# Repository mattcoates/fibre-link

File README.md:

# Optical Fibre Link Project

This repository contains the results and scripts used for the testing of our optical fibre link.

## Clock Recovery
Scripts and results of the tests carried out on the FPGA that was performing clock recovery.

## Error Rate
Testing of the BER of the complete link.

## Header Detection
Scripts and results of the tests on the header detector.

## Image Testing
Results of using the link to transmit an image at different frequencies. 

## PRBS
Characterisation of a pseudo-random number generator used to generate dummy data to test the link.

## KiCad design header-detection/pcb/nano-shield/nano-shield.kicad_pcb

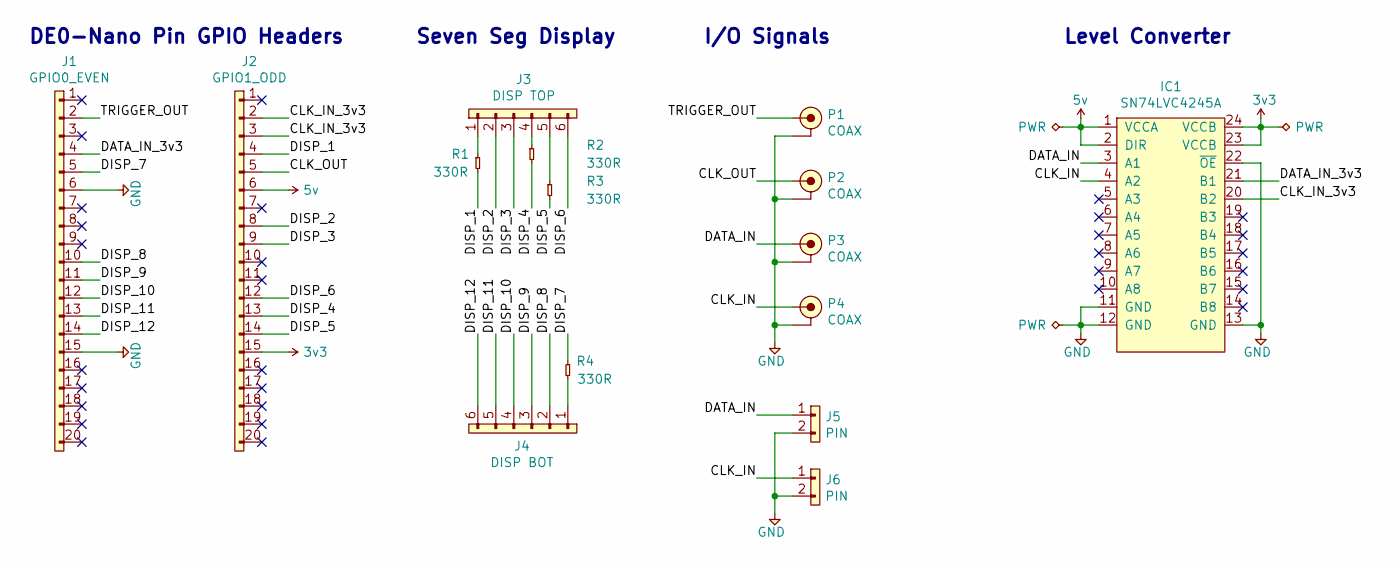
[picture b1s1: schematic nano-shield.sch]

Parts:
IC1: SN74LVC4245A; TSSOP-24; Farnell 1236393
J1: GPIO0_EVEN; SIL-254P-20
J2: GPIO1_ODD; SIL-254P-20
J3: DISP TOP; SIL-254P-06
J4: DISP BOT; SIL-254P-06
J5, J6: PIN; SIL-254P-02
P1, P2, P3, P4: COAX; SMA-EDGE; Farnell 1608592
R1, R2, R3, R4: 330R; 0805

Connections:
3v3: IC1.23 (VCCB), IC1.24 (VCCB), J2.15
5v: IC1.1 (VCCA), IC1.2 (DIR), J2.6
/CLK_IN: IC1.4 (A2), J6.1, P4.1 (RF)
/CLK_IN_3v3: IC1.20 (B2), J2.2, J2.3
/CLK_OUT: J2.5, P2.1 (RF)
/DATA_IN: IC1.3 (A1), J5.1, P3.1 (RF)
/DATA_IN_3v3: IC1.21 (B1), J1.4
/DISP_1: J2.4, R1.2
/DISP_2: J2.8, J3.2
/DISP_3: J2.9, J3.3
/DISP_4: J2.13, R2.2
/DISP_5: J2.14, R3.2
/DISP_6: J2.12, J3.6
/DISP_7: J1.5, R4.1
/DISP_8: J1.10, J4.2
/DISP_9: J1.11, J4.3
/DISP_10: J1.12, J4.4
/DISP_11: J1.13, J4.5
/DISP_12: J1.14, J4.6
/TRIGGER_OUT: J1.2, P1.1 (RF)
GND: IC1.11 (GND), IC1.12 (GND), IC1.13 (GND), IC1.22 (~OE), J1.6, J1.15, J5.2, J6.2, P1.2 (GND), P2.2 (GND), P3.2 (GND), P4.2 (GND)
unnamed: J3.1, R1.1
unnamed: J3.4, R2.1
unnamed: J3.5, R3.1
unnamed: J4.1, R4.2

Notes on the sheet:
DE0-Nano Pin GPIO Headers
Seven Seg Display
I/O Signals
Level Converter

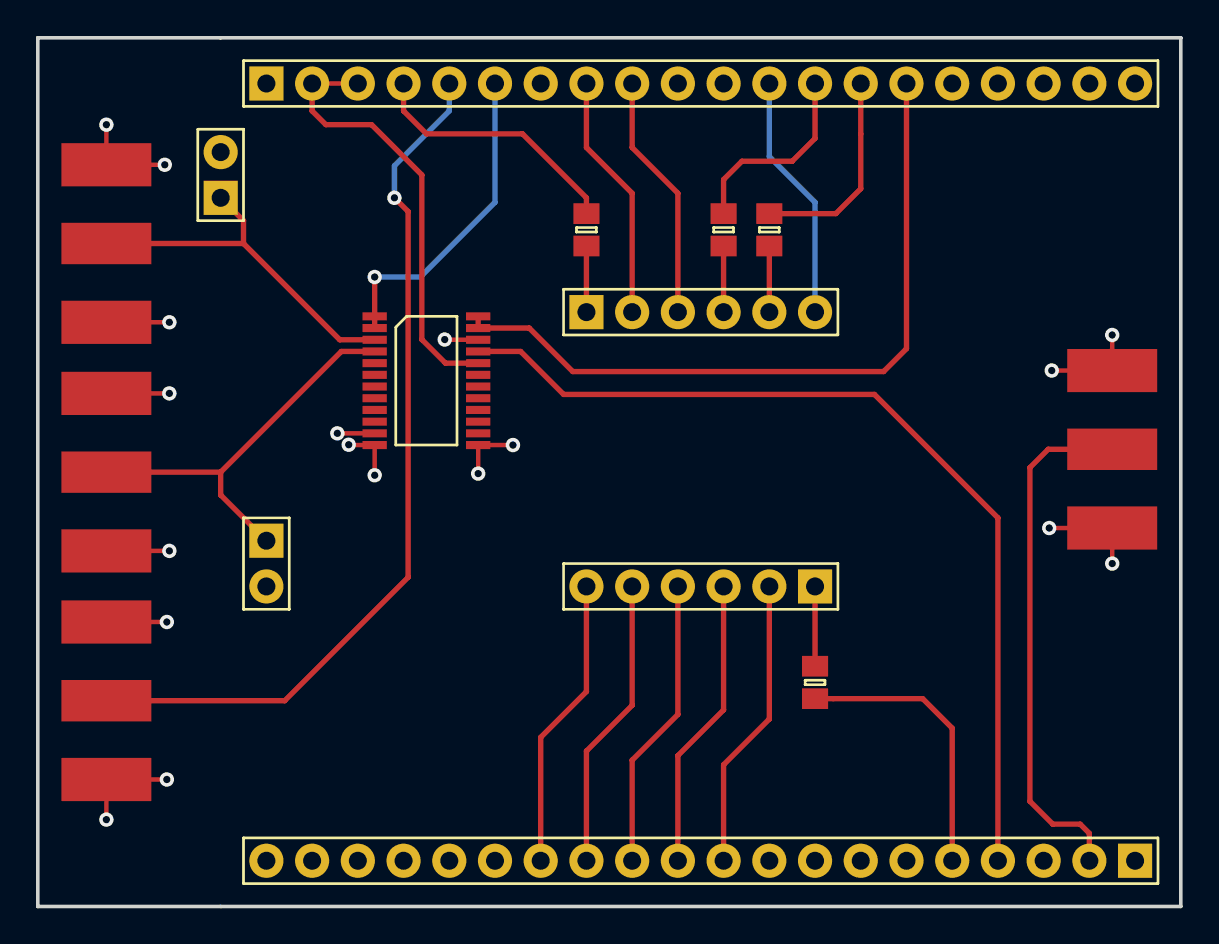
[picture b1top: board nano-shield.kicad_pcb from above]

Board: 2 copper layers, 63.5 x 48.3 mm, 15 parts (0 on the bottom side), 25 nets.

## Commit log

2018-05-11 first push
2018-05-11 changed readme
2018-05-11 modified test to consider all possible sequences, not just those spaced k apart
2018-05-11 added k as arg
2018-05-14 added fft
2018-05-14 added fft title
2018-05-15 built and analysed final circuit
2018-05-17 header detection working and verified
2018-05-17 added display headers per sec
2018-05-17 added fw folder
2018-05-21 added code for spinny thing header detector
2018-05-23 moved folders around
2018-05-23 deleted stm32 stuff, got fpga working and recorded capture to prove it
2018-05-23 tested header detection working at 1.6mhz
2018-05-24 added bit error rate tests
2018-05-25 completed link error rate tests
2018-05-25 added correct decoded output for 4mhz
2018-05-29 created de0-nano shield
2018-05-29 added clock recovery scripts
2018-05-30 added clock recovery testing
2018-05-31 image testing
2018-05-31 processed 7.8mhz image test
2018-06-01 more image testing
2018-06-04 16mhz image
2018-06-04 added 32mhz
